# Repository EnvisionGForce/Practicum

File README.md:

# ECE411 Practicum Project

**Team:** Envision GForce (Team 16)

**Members:** Thomas Harris, Jacbob Metoxen, Eric Schulte, Seth Starr

**Advisor:** Andrew Greenberg

**Project Description:** Intuitive Lateral G-Force Display (Direction and magnitude)

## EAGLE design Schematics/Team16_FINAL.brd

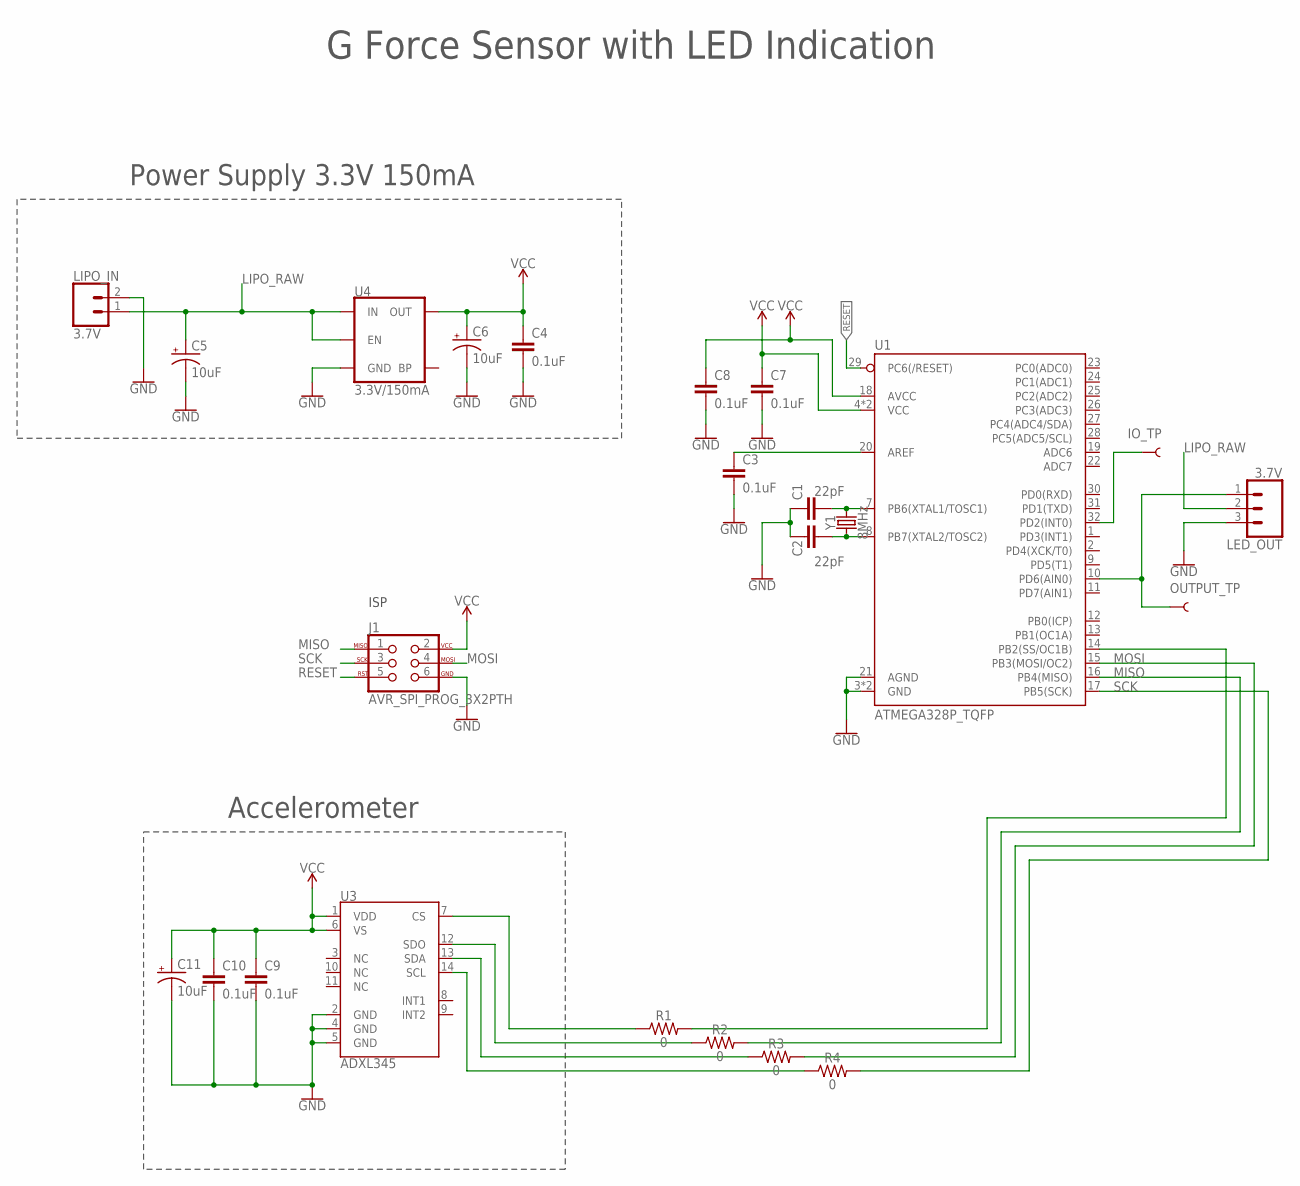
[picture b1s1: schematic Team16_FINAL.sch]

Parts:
C1, C2: 22pF; 0603
C3, C4, C7, C8, C9, C10: 0.1uF; 0402
C5, C6, C11: 10uF; 0603-POLAR
IO_TP: TEST-POINT3; PAD.03X.03
J1: AVR_SPI_PROG_3X2PTH; 2X3
LED_OUT: 3.7V; 1X03_LOCK_LONGPADS
LIPO_IN: 3.7V; 1X02_LONGPADS
OUTPUT_TP: TEST-POINT3; PAD.03X.03
R1, R2, R3, R4: 0; 0402
U1: ATMEGA328P_TQFP; TQFP32-08
U3: ADXL345; LGA-14
U4: 3.3V/150mA; SOT23-5
Y1: 8MHz; CRYSTAL-SMD-5X3.2-4PAD

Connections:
GND: C1.1, C2.1, C3.2, C4.2, C5.-, C6.-, C7.2, C8.2, C9.2, C10.2, C11.-, J1.6, LED_OUT.3, LIPO_IN.2, U1.3 (GND), U1.5 (GND), U1.21 (AGND), U3.2 (GND), U3.4 (GND), U3.5 (GND), U4.2 (GND)
LIPO_RAW: C5.+, LED_OUT.2, LIPO_IN.1, U4.1 (IN), U4.3 (EN)
MISO: J1.1, R2.2, U1.16 (PB4(MISO))
MOSI: J1.4, R3.2, U1.15 (PB3(MOSI/OC2))
unnamed: C1.2, U1.7 (PB6(XTAL1/TOSC1)), Y1.3 (2)
unnamed: C2.2, U1.8 (PB7(XTAL2/TOSC2)), Y1.1
unnamed: LED_OUT.1, OUTPUT_TP.P$1, U1.10 (PD6(AIN0))
unnamed: IO_TP.P$1, U1.32 (PD2(INT0))
unnamed: R1.1, U3.7 (CS)
unnamed: R2.1, U3.12 (SDO)
unnamed: R3.1, U3.13 (SDA)
unnamed: C3.1, U1.20 (AREF)
unnamed: R4.1, U3.14 (SCL)
unnamed: R1.2, U1.14 (PB2(SS/OC1B))
RESET: J1.5, U1.29 (PC6(/RESET))
SCK: J1.3, R4.2, U1.17 (PB5(SCK))
VCC: C4.1, C6.+, C7.1, C8.1, C9.1, C10.1, C11.+, J1.2, U1.4 (VCC), U1.6 (VCC), U1.18 (AVCC), U3.1 (VDD), U3.6 (VS), U4.5 (OUT)

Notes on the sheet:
ISP
Power Supply 3.3V 150mA
Accelerometer
G Force Sensor with LED Indication

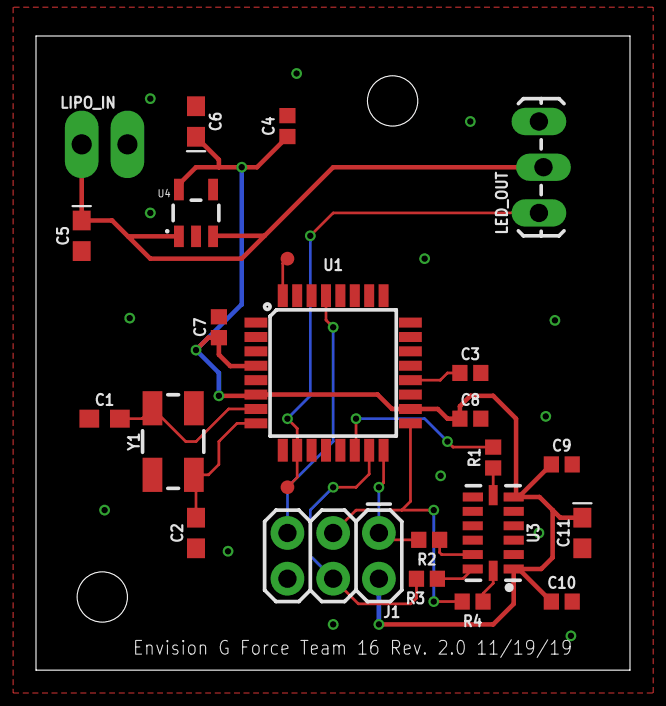
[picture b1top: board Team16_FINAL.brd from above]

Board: 2 copper layers, 33.0 x 35.2 mm, 24 parts (0 on the bottom side), 17 nets.

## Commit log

2019-10-13 Added asdf
    asdf
2019-10-17 Create Useful URLs
2019-10-17 Update Useful URLs
2019-10-18 Update 3x_Practicum_Ideas.txt
    Added my idea to the list.
2019-10-20 Create ex
2019-10-20 Add files via upload
    Moved Arduino Pro Mini datasheet to 'Datasheets' folder
2019-10-20 Rename 3x_Practicum_Ideas.txt to Practicum HW/3x_Practicum_Ideas.txt
2019-10-20 Delete Arduino-Pro-Mini-v14-1.pdf
    Deleted from main repository. See 'Datasheets' folder.
2019-10-20 Delete Notes10_15.pdf
    Deleted from main repository. See 'Meeting Notes' folder.
2019-10-29 Create Weekly Status Updates
2019-10-30 Update Weekly Status Updates
2019-10-30 Rename Weekly Status Updates to Weekly Status Updates Log
2019-10-30 Rename Weekly Status Updates Log to Weekly Status Updates/Weekly Status Updates Log
2019-11-07 Update Weekly Status Updates Log
2019-11-08 Rename Sch1r2.brd to Schematics/Sch1r2.brd
2019-11-08 measurements and DXF for LED fixture
    measurements taken using MicroVu with InSpec.
2019-11-10 LED RING DXF
    DXF for the case for the LED.
2019-11-10 Add files via upload
    What I have so far. Determines direction (in radians) and magnitude from input vector from ADXL345 in the form: 32, -24.
2019-11-14 Rename Sch1r2.brd to Schematics/Layout_rough.brd
2019-11-14 Create foo
2019-11-14 Rename Rev3.sch to Materials/Rev3.sch
2019-11-14 Rename Schematics/Layout_rough.brd to Materials/Layout_rough.brd
2019-11-14 Rename Rev3.sch to schematic_rough.sch
2019-11-14 Rename schematic_rough.sch to Schematic_rough.sch
2019-11-14 Rename Schematics/Sch1r2.sch to Materials/Sch1r2_new.sch
2019-11-19 Meeting_11_14
2019-11-30 Rename Code/ADXL345_test.ino to Code/Old/ADXL345_test.ino
2019-11-30 Rename Code/ADXL345_test_NEW.ino to Code/Old/ADXL345_test_NEW.ino
2019-11-30 Rename Code/ADXL345_test_w_LED.ino to Code/Old/ADXL345_test_w_LED.ino
2019-11-30 Rename Code/LED_test.ino to Code/Old/LED_test.ino
2019-11-30 Rename Code/accel-LED-interface.ino to Code/Old/accel-LED-interface.ino
2019-12-01 Rename Code/ADXL345_test_w_12LED.ino to Code/Old/ADXL345_test_w_12LED.ino

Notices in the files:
parts and their libraries:
SparkFun-Capacitors: Licensing: Creative Commons ShareAlike 4.0 International - https://creativecommons.org/licenses/by-sa/4.0
